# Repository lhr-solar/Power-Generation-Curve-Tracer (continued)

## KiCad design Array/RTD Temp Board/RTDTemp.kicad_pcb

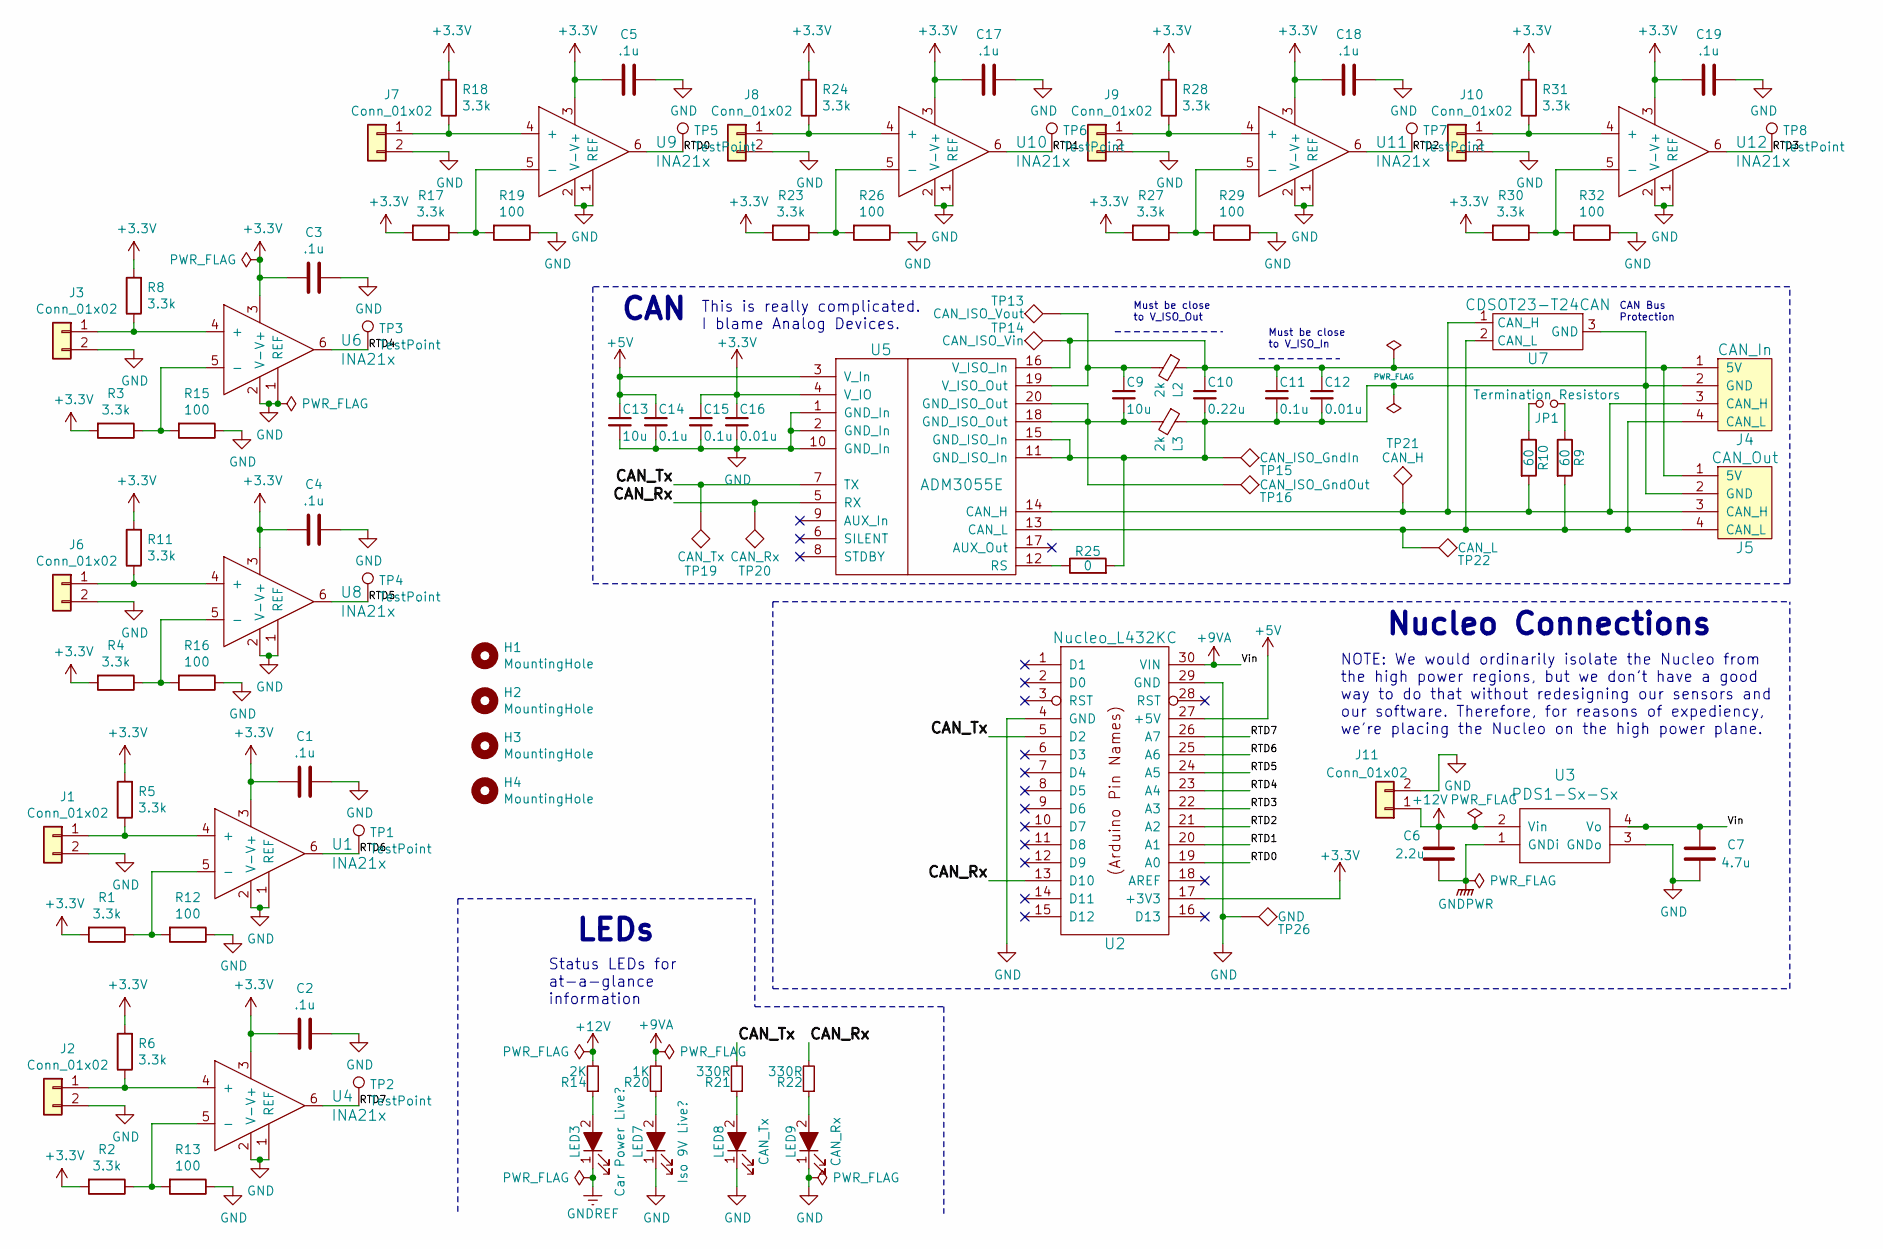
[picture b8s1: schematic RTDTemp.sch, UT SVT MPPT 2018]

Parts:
C1, C2, C3, C4, C5, C17, C18, C19: .1u; C_0805_2012Metric
C6: 2.2u; C_0805_2012Metric
C7: 4.7u; C_0805_2012Metric
C9, C13: 10u; C_0805_2012Metric
C10: 0.22u; C_0805_2012Metric
C11, C14, C15: 0.1u; C_0805_2012Metric
C12, C16: 0.01u; C_0805_2012Metric
H1, H2, H3, H4: MountingHole; MountingHole_3mm
J1, J2, J3, J6, J7, J8, J9, J10: Conn_01x02; Molex_Micro-Fit_3.0_43650-0200_1x02_P3.00mm_Horizontal
J4: CAN_In; Molex_MicroFit3.0_1x4xP3.00mm_PolarizingPeg_Vertical
J5: CAN_Out; Molex_MicroFit3.0_1x4xP3.00mm_PolarizingPeg_Vertical
J11: Conn_01x02; Molex_Micro-Fit_3.0_43650-0215_1x02_P3.00mm_Vertical
JP1: Termination Resistors; PinHeader_1x02_P2.54mm_Vertical
L2, L3: 2k; L_0805_2012Metric
LED3: Car Power Live?; LED_0805_2012Metric
LED7: Iso 9V Live?; LED_0805_2012Metric
LED8: CAN_Tx; LED_0805_2012Metric
LED9: CAN_Rx; LED_0805_2012Metric
R1, R2, R3, R4, R5, R6, R8, R11, R17, R18, R23, R24, R27, R28, R30, R31: 3.3k; R_0805_2012Metric
R9, R10: 60; R_0805_2012Metric
R12, R13, R15, R16, R19, R26, R29, R32: 100; R_0805_2012Metric
R14: 2K; R_0805_2012Metric
R20: 1K; R_0805_2012Metric
R21, R22: 330R; R_0805_2012Metric
R25: 0; R_0805_2012Metric
TP1, TP2, TP3, TP4, TP5, TP6, TP7, TP8: TestPoint; TestPoint_Keystone_5005-5009_Compact
TP13: CAN_ISO_Vout; TestPoint_Keystone_5005-5009_Compact
TP14: CAN_ISO_Vin; TestPoint_Keystone_5005-5009_Compact
TP15: CAN_ISO_GndIn; TestPoint_Keystone_5005-5009_Compact
TP16: CAN_ISO_GndOut; TestPoint_Keystone_5005-5009_Compact
TP19: CAN_Tx; TestPoint_Keystone_5005-5009_Compact
TP20: CAN_Rx; TestPoint_Keystone_5005-5009_Compact
TP21: CAN_H; TestPoint_Keystone_5005-5009_Compact
TP22: CAN_L; TestPoint_Keystone_5005-5009_Compact
TP26: GND; TestPoint_Keystone_5005-5009_Compact
U1, U4, U6, U8, U9, U10, U11, U12: INA21x; SOIC-6_1.40x2.15mm_Pitch0.65mm
U2: Nucleo_L432KC; NucleoL432KC
U3: PDS1-Sx-Sx; PDSx-S
U5: ADM3055E; SOIC-20W_7.5x15.4mm_Pitch1.27mm
U7: CDSOT23-T24CAN; SOT-23W_Handsoldering

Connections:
+3V3: C1.2, C2.2, C3.2, C4.2, C5.2, C15.1, C16.1, C17.2, C18.2, C19.2, R1.2, R2.2, R3.2, R4.2, R5.2, R6.2, R8.2, R11.2, R17.2, R18.2, R23.2, R24.2, R27.2, R28.2, R30.2, R31.2, U1.3 (V+), U2.17 (+3V3), U4.3 (V+), U5.4 (V_IO), U6.3 (V+), U8.3 (V+), U9.3 (V+), U10.3 (V+), U11.3 (V+), U12.3 (V+)
+5V: C13.1, C14.1, U2.27 (+5V), U5.3 (V_In)
+9VA: C7.1, R20.2, U2.30 (VIN), U3.4 (Vo)
+12V: C6.1, J11.1, R14.2, U3.2 (Vin)
/CAN_Rx: R22.2, TP20.1, U2.13 (D10), U5.5 (RX)
/CAN_Tx: R21.2, TP19.1, U2.5 (D2), U5.7 (TX)
/RTD0: TP5.1, U2.19 (A0), U9.6; also elsewhere on the board
/RTD1: TP6.1, U2.20 (A1), U10.6
/RTD2: TP7.1, U2.21 (A2), U11.6
/RTD3: TP8.1, U2.22 (A3), U12.6
/RTD4: TP3.1, U2.23 (A4), U6.6
/RTD5: TP4.1, U2.24 (A5), U8.6
/RTD6: TP1.1, U1.6, U2.25 (A6)
/RTD7: TP2.1, U2.26 (A7), U4.6
GND: C1.1, C2.1, C3.1, C4.1, C5.1, C7.2, C13.2, C14.2, C15.2, C16.2, C17.1, C18.1, C19.1, J1.2, J2.2, J3.2, J6.2, J7.2, J8.2, J9.2, J10.2, J11.2, LED7.1 (K), LED8.1 (K), LED9.1 (K), R12.1, R13.1, R15.1, R16.1, R19.1, R26.1, R29.1, R32.1, TP26.1, U1.1 (REF), U1.2 (V-), U2.4 (GND), U2.29 (GND), U3.3 (GNDo), U4.1 (REF), U4.2 (V-), U5.1 (GND_In), U5.2 (GND_In), U5.10 (GND_In), U6.1 (REF), U6.2 (V-), U8.1 (REF), U8.2 (V-), U9.1 (REF), U9.2 (V-), U10.1 (REF), U10.2 (V-), U11.1 (REF), U11.2 (V-), U12.1 (REF), U12.2 (V-)
GNDPWR: C6.2, U3.1 (GNDi)
GNDREF: LED3.1 (K)
unnamed: C9.1, L2.2, TP13.1, U5.19 (V_ISO_Out)
unnamed: C9.2, L3.2, TP16.1, U5.18 (GND_ISO_Out), U5.20 (GND_ISO_Out)
unnamed: C10.1, C11.1, C12.1, J4.1 (5V), J5.1 (5V), L2.1, TP14.1, U5.16 (V_ISO_In)
unnamed: C10.2, C11.2, C12.2, J4.2 (GND), J5.2 (GND), L3.1, R25.2, TP15.1, U5.11 (GND_ISO_In), U5.15 (GND_ISO_In), U7.3 (GND)
unnamed: J1.1, R5.1, U1.4 (+)
unnamed: J2.1, R6.1, U4.4 (+)
unnamed: J3.1, R8.1, U6.4 (+)
unnamed: J4.3 (CAN_H), J5.3 (CAN_H), R10.2, TP21.1, U5.14 (CAN_H), U7.1 (CAN_H)
unnamed: J4.4 (CAN_L), J5.4 (CAN_L), R9.2, TP22.1, U5.13 (CAN_L), U7.2 (CAN_L)
unnamed: J6.1, R11.1, U8.4 (+)
unnamed: J7.1, R18.1, U9.4 (+)
unnamed: J8.1, R24.1, U10.4 (+)
unnamed: J9.1, R28.1, U11.4 (+)
unnamed: J10.1, R31.1, U12.4 (+)
unnamed: JP1.1, R9.1
unnamed: JP1.2, R10.1
unnamed: LED3.2 (A), R14.1
unnamed: LED7.2 (A), R20.1
unnamed: LED8.2 (A), R21.1
unnamed: LED9.2 (A), R22.1
unnamed: R1.1, R12.2, U1.5 (-)
unnamed: R2.1, R13.2, U4.5 (-)
unnamed: R3.1, R15.2, U6.5 (-)
unnamed: R4.1, R16.2, U8.5 (-)
unnamed: R17.1, R19.2, U9.5 (-)
unnamed: R23.1, R26.2, U10.5 (-)
unnamed: R25.1, U5.12 (RS)
unnamed: R27.1, R29.2, U11.5 (-)
unnamed: R30.1, R32.2, U12.5 (-)

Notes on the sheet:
Nucleo Connections
NOTE: We would ordinarily isolate the Nucleo from the high power regions, but we don't have a good way to do that without redesigning our sensors and our software. Therefore, for reasons of expediency, we're placing the Nucleo on the high power plane.
CAN
This is really complicated. I blame Analog Devices.
Must be close to V_ISO_Out
Must be close to V_ISO_In
LEDs
Status LEDs for at-a-glance information
CAN Bus Protection

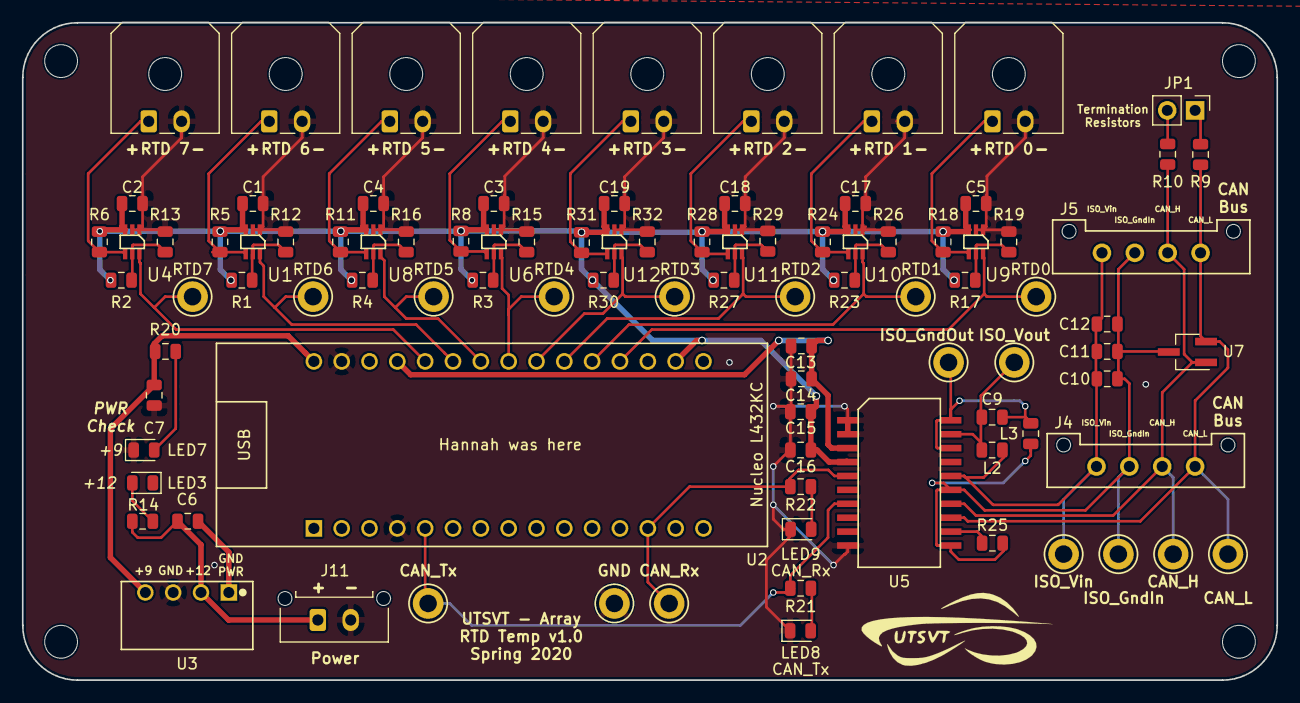
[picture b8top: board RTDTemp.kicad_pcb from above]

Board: 2 copper layers, 114.5 x 60.0 mm, 100 parts (0 on the bottom side), 45 nets.

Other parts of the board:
RTD0: TestPoint; TestPoint_Keystone_5005-5009_Compact

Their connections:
/RTD0: RTD0.1; also elsewhere on the board

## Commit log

2019-02-07 Organized repo.
2019-02-07 Added README.md file
2019-02-09 Created images of schematic/PCB
2019-02-09 New Debugger for BPS
2019-02-10 Relative addressing for schematic files
2019-02-12 Edited inductor choke in BPS master.
2019-02-14 Create pdf of schematics of BPS master.
2019-02-15 Changed the connectors to stack
2019-02-15 New connector for Temperature Board for BPS
2019-02-16 Edited BPS temperature board to have stackable connectors.
2019-02-16 Edited comm pins of BPS voltage in case of stacking issues.
2019-02-16 fix hierarchy
2019-02-16 NC flags, 3.3v flag, etc.
2019-02-16 Added the USB debugging board design.
2019-02-19 debugger
2019-02-19 Added labels to USB breakout.
2019-02-19 Created gerber zip file.
2019-02-19 Created gerber files
2019-02-23 Updated connectors **Use new netlist**
2019-02-23 fixed bugs
2019-02-24 Finished debugger layout. Still needs annotations.
2019-02-25 Fixed temperature board for BPS.
2019-02-27 Redid the footprint for the IC, rerouted.
2019-02-27 New footprint for the LTC6811
2019-03-02 Test
2019-03-02 debugger beautify
2019-03-02 usb c
2019-03-04 Updated LTC6811 footprint.
2019-03-04 board updated with usb c
2019-03-09 Old Current Sensor Board
2019-03-09 board updated
2019-03-09 Updated BPS pcbs.
2019-03-09 dashboard
2019-03-09 contactors
2019-03-14 planes added
2019-03-18 Changed values of caps in Master board of BPS.
2019-03-20 Changed capacitor value for 3.3V regulator in BPS master.
2019-03-21 Dashboard v2
2019-03-25 footprint error fixed in voltage board. Created new gerber files.
2019-03-30 Fixed some stuff
2019-03-30 BOM for Temperature
2019-03-30 planes updated
2019-03-30 Modified Low-Pass Filter values
2019-03-30 12V and gndpower planes
2019-03-30 planes
2019-03-31 rounded corners
2019-04-06 debugger silk screen
2019-04-06 Temperature sensor distribution board
2019-04-07 fuse board schematic
2019-04-13 fuse board
2019-06-08 Edited temmperature board to have reset pin to high.
2019-07-27 Adds Nucleo version of master board.
2019-08-31 Adds Display board schematics.
2019-08-31 Delete
2019-08-31 Some suggested changes and smaller
2019-08-31 Creates schematics for display.
2019-08-31 reduced size of current board
2019-08-31 Display, Board Layout
2019-09-07 New Current Board, Removed sensing, new connector
2019-09-14 TM4C-Based master board.
2019-09-14 worked on pcb layout and schematic
2019-09-21 Adds display board
2019-09-21 Added Mounting Holes to Temperature Power Board
2019-09-21 Finish Display board, generate Gerbers.
2019-10-11 Creates gerber files for display board and master.
2019-10-11 Deletes unnecessary boards.
2019-10-11 Adds master board v1.1.
2019-10-12 Change capacitor value for VCAP on master board to 4.7uF
2019-10-12 Fix the backwardness to the Temperature power board
2019-10-26 Adds Minion board pcb for BPS.
2019-10-27 Removes Minion boards for next tag.
2019-10-27 Cleans repo to only contain most recent design.
2019-10-27 Adds pdf schematics of Minion boards.
2019-12-25 Edits master board to not have temperature board pinouts.
2020-01-14 Adds contactor driver board for precharge motor and array.
2020-01-25 Adds BPS master board with no temperature brd electronics and ContactorDriver for dashboard to control.
2020-01-25 Adds resistor mount. Need to add pheonix connector.
2020-01-31 Adds final BPS leader board and completed Contactor/precharge board.
2020-02-01 Adds hole dimenions silkscreen text for contactor driver board.
2020-02-15 "Test, Scrutineering, and RTD Temp Board"
2020-02-29 Editing Array and Starting Telemetry board
2020-03-01 Editing Array Board and telemetry board
2020-03-07 Finished Telemetry Board
2020-03-07 Zip files for Telemetry
2020-03-07 More zip files
2020-04-29 Adding PDB and PBB
2020-05-18 Add motor regulator board
2020-08-02 Current board (#41)
    * Adds current board project
    * Found footprint and symbol
    * Finished basic connections. Still need to add DC-DC converter and connection for interrupts if needed.
    * Completes schematic of current board
    * Adds AS8510 into utsvt-bps.lib
    * Edits name of mounting holes to standardized M3 screw size
2020-08-02 Leader board (#42)
    * Creates fan brd interface schematics and updates symbols/footprints related to the leader board
    * Finishes schematics for bps leader board
    * Renames bps master to bps leader:
    * Places most components of leader board in their respective locations with nothing traced
    * Adds power planes
    * Everything traced in leader board except for power circuitry
2020-08-09 removed old files.
2020-08-09 Added curve tracer files
2020-08-09 CAN updated, needs bugfixes and footprint review.
2020-08-12 proof checked, drc run and mounting holes added.
2020-08-21 rebuilt with MOSFET footprint flipped, traces rewired, and dot for every smd component where 1st pin is not obvious
2020-08-28 moved ADC_V pin down two
2020-12-16 Major Curve Tracer Board overhaul. Schematic advanced to Rev 1.1.0. Layout advanced to Rev 1.1.0. Parts list advanced to Rev 1.1.0.
2021-01-13 Addressed review.
2021-10-21 added bodge notes to current version Curve Tracer
2022-02-02 v1.2.0 rc with new layout.
2022-02-02 theme change, ibom, pdfs, outputs generated.
2022-02-08 swapped INA210 to SC70 footprint, added gate resistor
2022-02-11 regenerated outputs and labeled output zip.
2022-02-11 README update.
2022-02-17 gerber rebuilds to fix JLCPCB error
2022-08-26 restructuring
2022-08-26 add backup folder
2023-05-20 cleanup and fix errors for v1.3.0, proposed v1.4.0
2023-05-20 reorg project directory, moved in fw files
2023-05-20 rm old kicad proj ref
2023-05-20 mv changelog into docs
2023-09-16 Updated main w/ comm capability w/ Eclipse 0.3
2023-10-28 Update README.md
    fixed my name
2023-12-17 Update main.cpp
    just a practice commit with no real changes to the code
2025-02-27 set up baud rate and capture conf receiver methods
